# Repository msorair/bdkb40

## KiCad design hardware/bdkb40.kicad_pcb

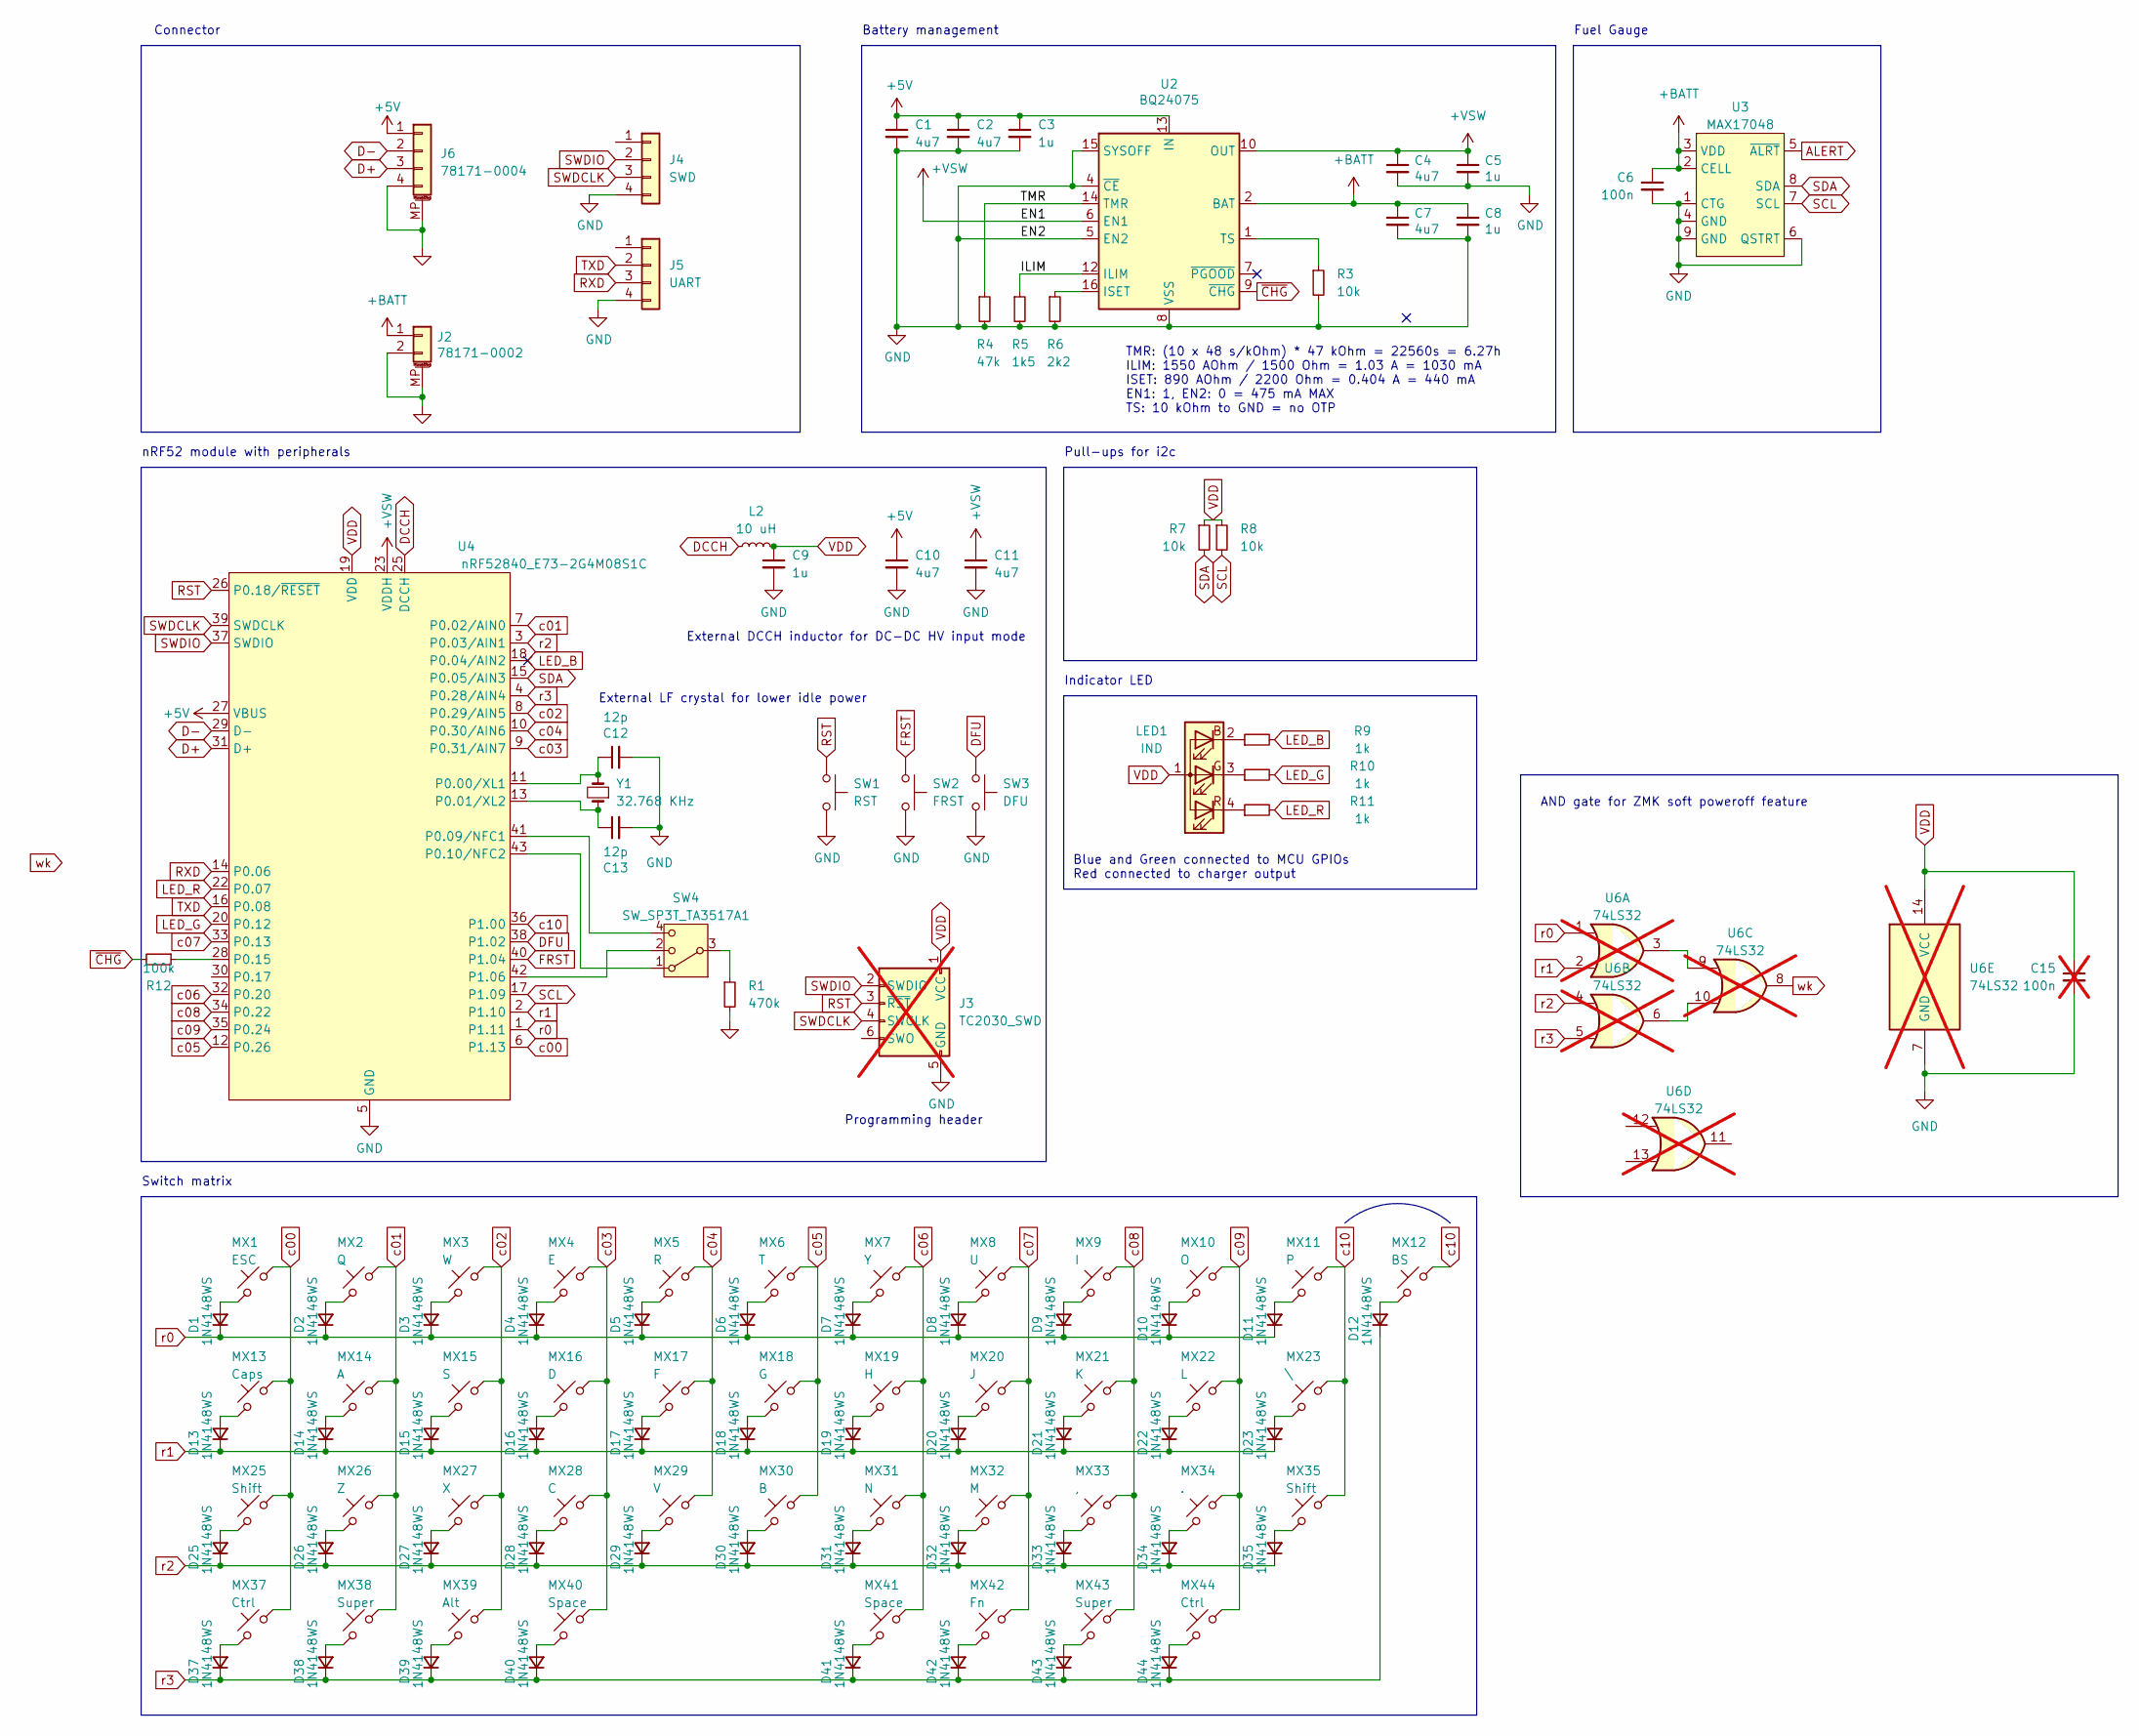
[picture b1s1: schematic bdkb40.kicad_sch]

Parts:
C1, C2, C4, C7, C10, C11: 4u7; C_0402_1005Metric; LCSC C23733
C3, C5, C8, C9: 1u; C_0402_1005Metric; LCSC C52923
C6: 100n; C_0402_1005Metric; LCSC C307331
C12, C13: 12p; C_0402_1005Metric; LCSC C1547
C15: 100n; C_0402_1005Metric; LCSC C307331; not fitted
D1, D2, D3, D4, D5, D6, D7, D8, D9, D10, D11, D12, D13, D14, D15, D16, D17, D18, D19, D20, D21, D22, D23, D25, D26, D27, D28, D29, D30, D31, D32, D33, D34, D35, D37, D38, D39, D40, D41, D42, D43, D44: 1N4148WS; D_SOD-323; LCSC C2128
J2: 78171-0002; Molex_Pico-EZmate_78171-0002_1x02-1MP_P1.20mm_Vertical; LCSC C505023
J3: TC2030_SWD; CON_TC2030_outlined; not fitted
J4: SWD; PinHeader_1x04_P2.54mm_Vertical
J5: UART; PinHeader_1x04_P2.54mm_Vertical
J6: 78171-0004; Molex_Pico-EZmate_78171-0004_1x04-1MP_P1.20mm_Vertical; LCSC C588524
L2: 10 uH; L_0603_1608Metric; LCSC C92982
LED1: IND; LED_1206R; LCSC C2802677
MX1: ESC; SW_MX_HS_CPG151101S11_1u; LCSC C5184526
MX2: Q; SW_MX_HS_CPG151101S11_1u; LCSC C5184526
MX3: W; SW_MX_HS_CPG151101S11_1u; LCSC C5184526
MX4: E; SW_MX_HS_CPG151101S11_1u; LCSC C5184526
MX5: R; SW_MX_HS_CPG151101S11_1u; LCSC C5184526
MX6: T; SW_MX_HS_CPG151101S11_1u; LCSC C5184526
MX7: Y; SW_MX_HS_CPG151101S11_1u; LCSC C5184526
MX8: U; SW_MX_HS_CPG151101S11_1u; LCSC C5184526
MX9: I; SW_MX_HS_CPG151101S11_1u; LCSC C5184526
MX10: O; SW_MX_HS_CPG151101S11_1u; LCSC C5184526
MX11: P; SW_MX_HS_CPG151101S11_1u; LCSC C5184526
MX12: BS; SW_MX_HS_CPG151101S11_1u; LCSC C5184526
MX13: Caps; SW_MX_HS_CPG151101S11_1.25u; LCSC C5184526
MX14: A; SW_MX_HS_CPG151101S11_1u; LCSC C5184526
MX15: S; SW_MX_HS_CPG151101S11_1u; LCSC C5184526
MX16: D; SW_MX_HS_CPG151101S11_1u; LCSC C5184526
MX17: F; SW_MX_HS_CPG151101S11_1u; LCSC C5184526
MX18: G; SW_MX_HS_CPG151101S11_1u; LCSC C5184526
MX19: H; SW_MX_HS_CPG151101S11_1u; LCSC C5184526
MX20: J; SW_MX_HS_CPG151101S11_1u; LCSC C5184526
MX21: K; SW_MX_HS_CPG151101S11_1u; LCSC C5184526
MX22: L; SW_MX_HS_CPG151101S11_1u; LCSC C5184526
MX23: \; SW_MX_HS_CPG151101S11_1.75u; LCSC C5184526
MX25: Shift; SW_MX_HS_CPG151101S11_1.75u; LCSC C5184526
MX26: Z; SW_MX_HS_CPG151101S11_1u; LCSC C5184526
MX27: X; SW_MX_HS_CPG151101S11_1u; LCSC C5184526
MX28: C; SW_MX_HS_CPG151101S11_1u; LCSC C5184526
MX29: V; SW_MX_HS_CPG151101S11_1u; LCSC C5184526
MX30: B; SW_MX_HS_CPG151101S11_1u; LCSC C5184526
MX31: N; SW_MX_HS_CPG151101S11_1u; LCSC C5184526
MX32: M; SW_MX_HS_CPG151101S11_1u; LCSC C5184526
MX33: ,; SW_MX_HS_CPG151101S11_1u; LCSC C5184526
MX34: .; SW_MX_HS_CPG151101S11_1u; LCSC C5184526
MX35: Shift; SW_MX_HS_CPG151101S11_1.25u; LCSC C5184526
MX37, MX44: Ctrl; SW_MX_HS_CPG151101S11_1.25u; LCSC C5184526
MX38, MX43: Super; SW_MX_HS_CPG151101S11_1u; LCSC C5184526
MX39: Alt; SW_MX_HS_CPG151101S11_1.25u; LCSC C5184526
MX40: Space; SW_MX_HS_CPG151101S11_2.25u; LCSC C5184526
MX41: Space; SW_MX_HS_CPG151101S11_2.75u; LCSC C5184526
MX42: Fn; SW_MX_HS_CPG151101S11_1.25u; LCSC C5184526
R1: 470k; R_0402_1005Metric; LCSC C23164
R3: 10k; R_0402_1005Metric; LCSC C25197
R4: 47k; R_0402_1005Metric; LCSC C25792
R5: 1k5; R_0402_1005Metric; LCSC C25867
R6: 2k2; R_0402_1005Metric; LCSC C25879
R7, R8: 10k; R_0402_1005Metric; LCSC C25744
R9, R10, R11: 1k; R_0402_1005Metric; LCSC C11702
R12: 100k; R_0402_1005Metric; LCSC C25744
SW1: RST; SW_SPST_TS-1088-xR025; LCSC C720477
SW2: FRST; SW_SPST_TS-1088-xR025; LCSC C720477
SW3: DFU; SW_SPST_TS-1088-xR025; LCSC C720477
SW4: SW_SP3T_TA3517A1; SW_SP3T_PCM13; LCSC C514001
U2: BQ24075; VQFN-16-1EP_3x3mm_P0.5mm_EP1.6x1.6mm; LCSC C15464
U3: MAX17048; DFN-8-1EP_2x2mm_P0.5mm_EP0.7x1.3mm; LCSC C2682616
U4: nRF52840_E73-2G4M08S1C; LCSC C356849
U6: 74LS32; DIP-14_W7.62mm_SMDSocket_SmallPads; not fitted
Y1: 32.768 KHz; Crystal_SMD_2012-2Pin_2.0x1.2mm; LCSC C20148

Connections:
+5V: C1.1, C2.1, C3.1, C10.1, J6.1, U2.13 (IN), U4.27 (VBUS)
+BATT: C6.1, C7.1, C8.1, J2.1, U2.2 (BAT), U2.3 (BAT), U3.2 (CELL), U3.3 (VDD)
+VSW: C4.1, C5.1, C11.1, U2.6 (EN1), U2.10 (OUT), U2.11 (OUT), U4.23 (VDDH)
/ILIM: R5.1, U2.12 (ILIM)
/TMR: R4.1, U2.14 (TMR)
ALERT: U3.5 (~ALRT)
D+: J6.3, U4.31 (D+)
D-: J6.2, U4.29 (D-)
DCCH: L2.1, U4.25 (DCCH)
DFU: SW3.1, U4.38 (P1.02)
FRST: SW2.1, U4.40 (P1.04)
GND: C1.2, C2.2, C3.2, C4.2, C5.2, C6.2, C7.2, C8.2, C9.2, C10.2, C11.2, C12.2, C13.2, C15.2, J2.2, J2.MP (MountPin), J3.5 (GND), J4.4, J5.4, J6.4, J6.MP (MountPin), R1.2, R3.2, R4.2, R5.2, R6.2, SW1.2, SW2.2, SW3.2, U2.4 (~CE), U2.5 (EN2), U2.8 (VSS), U2.15 (SYSOFF), U2.17 (VSS), U3.1 (CTG), U3.4 (GND), U3.6 (QSTRT), U3.9 (GND), U4.5 (GND), U4.21 (GND), U4.24 (GND), U6.7 (GND)
LED_B: R9.2, U4.18 (P0.04/AIN2)
LED_G: R10.2, U4.20 (P0.12)
LED_R: R11.2, U4.22 (P0.07)
unnamed: D1.2 (A), MX1.1
unnamed: D2.2 (A), MX2.1
unnamed: D3.2 (A), MX3.1
unnamed: D4.2 (A), MX4.1
unnamed: D5.2 (A), MX5.1
unnamed: D6.2 (A), MX6.1
unnamed: D7.2 (A), MX7.1
unnamed: D8.2 (A), MX8.1
unnamed: D9.2 (A), MX9.1
unnamed: D10.2 (A), MX10.1
unnamed: D11.2 (A), MX11.1
unnamed: D12.2 (A), MX12.1
unnamed: D13.2 (A), MX13.1
unnamed: D14.2 (A), MX14.1
unnamed: D15.2 (A), MX15.1
unnamed: D16.2 (A), MX16.1
unnamed: D17.2 (A), MX17.1
unnamed: D18.2 (A), MX18.1
unnamed: D19.2 (A), MX19.1
unnamed: D20.2 (A), MX20.1
unnamed: D21.2 (A), MX21.1
unnamed: D22.2 (A), MX22.1
unnamed: D23.2 (A), MX23.1
unnamed: D25.2 (A), MX25.1
unnamed: D26.2 (A), MX26.1
unnamed: D27.2 (A), MX27.1
unnamed: D28.2 (A), MX28.1
unnamed: D29.2 (A), MX29.1
unnamed: D30.2 (A), MX30.1
unnamed: D31.2 (A), MX31.1
unnamed: D32.2 (A), MX32.1
unnamed: D33.2 (A), MX33.1
unnamed: D34.2 (A), MX34.1
unnamed: D35.2 (A), MX35.1
unnamed: D37.2 (A), MX37.1
unnamed: D38.2 (A), MX38.1
unnamed: D39.2 (A), MX39.1
unnamed: D40.2 (A), MX40.1
unnamed: D41.2 (A), MX41.1
unnamed: D42.2 (A), MX42.1
unnamed: D43.2 (A), MX43.1
unnamed: D44.2 (A), MX44.1
unnamed: LED1.2 (BK), R9.1
unnamed: LED1.3 (GK), R10.1
unnamed: LED1.4 (RK), R11.1
unnamed: R1.1, SW4.3
unnamed: R6.1, U2.16 (ISET)
unnamed: R3.1, U2.1 (TS)
unnamed: C12.1, U4.11 (P0.00/XL1), Y1.2
unnamed: C13.1, U4.13 (P0.01/XL2), Y1.1
unnamed: SW4.4, U4.41 (P0.09/NFC1)
unnamed: SW4.1, U4.43 (P0.10/NFC2)
unnamed: R12.1, U4.28 (P0.15)
unnamed: SW4.2, U4.42 (P1.06)
unnamed: U6.3, U6.9
unnamed: U6.6, U6.10
RST: J3.3 (~RST), SW1.1, U4.26 (P0.18/~RESET)
RXD: J5.3, U4.14 (P0.06)
SCL: R8.2, U3.7 (SCL), U4.17 (P1.09)
SDA: R7.2, U3.8 (SDA), U4.15 (P0.05/AIN3)
SWDCLK: J3.4 (SWCLK), J4.3, U4.39 (SWDCLK)
SWDIO: J3.2 (SWDIO), J4.2, U4.37 (SWDIO)
TXD: J5.2, U4.16 (P0.08)
VDD: C9.1, C15.1, J3.1 (VCC), L2.2, LED1.1 (A), R7.1, R8.1, U4.19 (VDD), U6.14 (VCC)
c00: MX1.2, MX13.2, MX25.2, MX37.2, U4.6 (P1.13)
c01: MX2.2, MX14.2, MX26.2, MX38.2, U4.7 (P0.02/AIN0)
c02: MX3.2, MX15.2, MX27.2, MX39.2, U4.8 (P0.29/AIN5)
c03: MX4.2, MX16.2, MX28.2, MX40.2, U4.9 (P0.31/AIN7)
c04: MX5.2, MX17.2, MX29.2, U4.10 (P0.30/AIN6)
c05: MX6.2, MX18.2, MX30.2, U4.12 (P0.26)
c06: MX7.2, MX19.2, MX31.2, MX41.2, U4.32 (P0.20)
c07: MX8.2, MX20.2, MX32.2, MX42.2, U4.33 (P0.13)
c08: MX9.2, MX21.2, MX33.2, MX43.2, U4.34 (P0.22)
c09: MX10.2, MX22.2, MX34.2, MX44.2, U4.35 (P0.24)
c10: MX11.2, MX12.2, MX23.2, MX35.2, U4.36 (P1.00)
r0: D1.1 (K), D2.1 (K), D3.1 (K), D4.1 (K), D5.1 (K), D6.1 (K), D7.1 (K), D8.1 (K), D9.1 (K), D10.1 (K), D11.1 (K), U4.1 (P1.11), U6.1
r1: D13.1 (K), D14.1 (K), D15.1 (K), D16.1 (K), D17.1 (K), D18.1 (K), D19.1 (K), D20.1 (K), D21.1 (K), D22.1 (K), D23.1 (K), U4.2 (P1.10), U6.2
r2: D25.1 (K), D26.1 (K), D27.1 (K), D28.1 (K), D29.1 (K), D30.1 (K), D31.1 (K), D32.1 (K), D33.1 (K), D34.1 (K), D35.1 (K), U4.3 (P0.03/AIN1), U6.4
r3: D12.1 (K), D37.1 (K), D38.1 (K), D39.1 (K), D40.1 (K), D41.1 (K), D42.1 (K), D43.1 (K), D44.1 (K), U4.4 (P0.28/AIN4), U6.5
~CHG: R12.2, U2.9 (~CHG)

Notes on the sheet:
AND gate for ZMK soft poweroff feature
Indicator LED
Pull-ups for i2c
External DCCH inductor for DC-DC HV input mode
Programming header
Blue and Green connected to MCU GPIOs Red connected to charger output
Connector
TMR: (10 x 48 s/kOhm) * 47 kOhm = 22560s = 6.27h ILIM: 1550 AOhm / 1500 Ohm = 1.03 A = 1030 mA ISET: 890 AOhm / 2200 Ohm = 0.404 A = 440 mA EN1: 1, EN2: 0 = 475 mA MAX TS: 10 kOhm to GND = no OTP
Switch matrix
Fuel Gauge
Battery management
nRF52 module with peripherals
External LF crystal for lower idle power

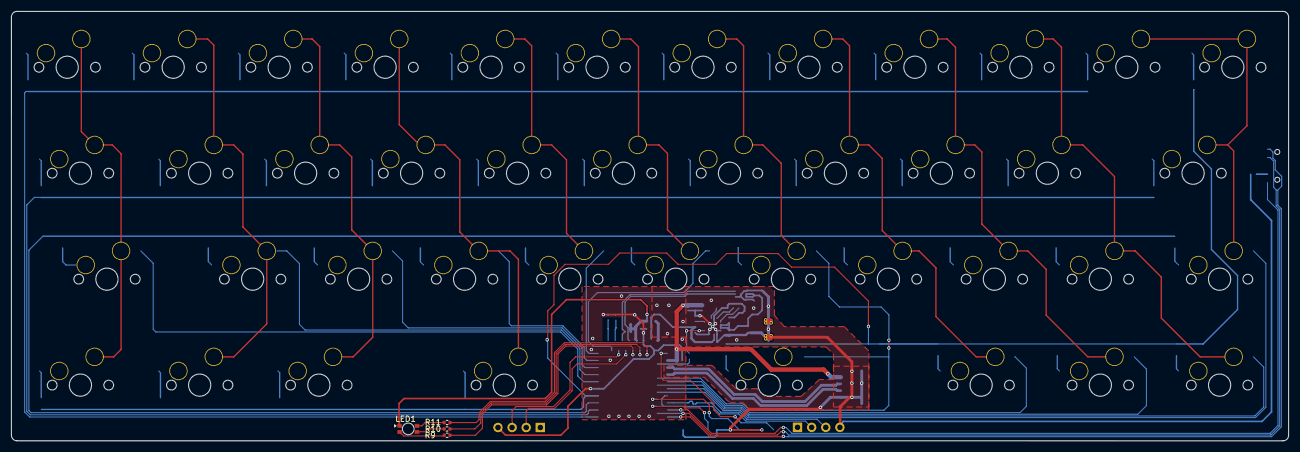
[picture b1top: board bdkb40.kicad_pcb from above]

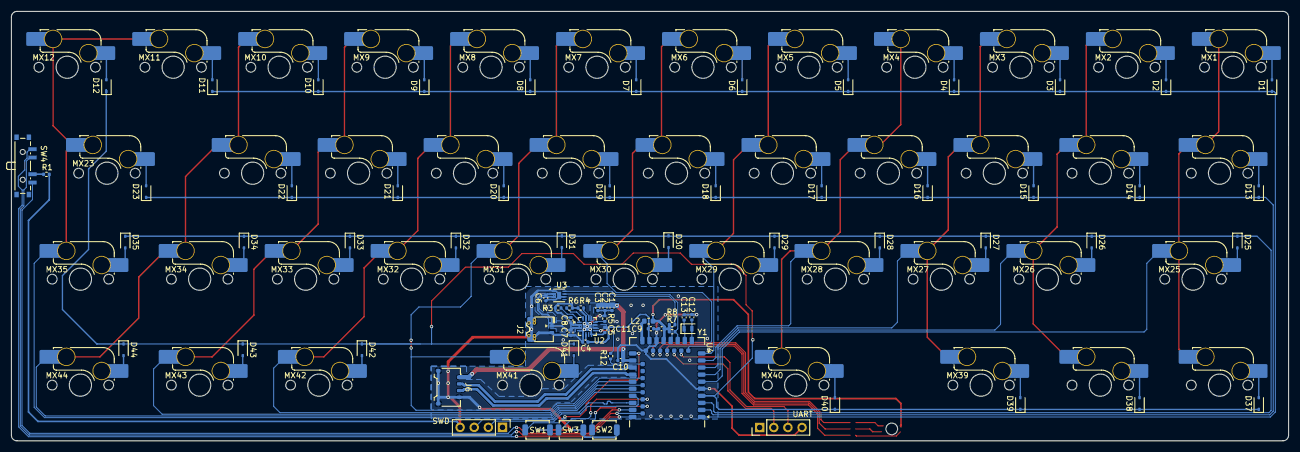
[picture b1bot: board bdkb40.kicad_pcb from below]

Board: 2 copper layers, 229.6 x 77.2 mm, 122 parts (118 on the bottom side), 92 nets.

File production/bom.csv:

Designator,Footprint,Quantity,Value,LCSC Part #
"C1, C10, C11, C2, C4, C7",0402,6,4u7,C23733
"C12, C13",0402,2,12p,C1547
"C3, C5, C8, C9",0402,4,1u,C52923
C6,0402,1,100n,C307331
"D1, D10, D11, D12, D13, D14, D15, D16, D17, D18, D19, D2, D20, D21, D22, D23, D25, D26, D27, D28, D29, D3, D30, D31, D32, D33, D34, D35, D37, D38, D39, D4, D40, D41, D42, D43, D44, D5, D6, D7, D8, D9",D_SOD-323,42,1N4148WS,C2128
J2,Molex_Pico-EZmate_78171-0002_1x02-1MP_P1.20mm_Vertical,1,78171-0002,C505023
J4,PinHeader_1x04_P2.54mm_Vertical,1,SWD,
J5,PinHeader_1x04_P2.54mm_Vertical,1,UART,
J6,Molex_Pico-EZmate_78171-0004_1x04-1MP_P1.20mm_Vertical,1,78171-0004,C588524
L2,0603,1,10 uH,C92982
LED1,LED_1206R,1,IND,C2802677
MX1,SW_MX_HS_CPG151101S11_1u,1,ESC,C5184526
MX10,SW_MX_HS_CPG151101S11_1u,1,O,C5184526
MX11,SW_MX_HS_CPG151101S11_1u,1,P,C5184526
MX12,SW_MX_HS_CPG151101S11_1u,1,BS,C5184526
MX13,SW_MX_HS_CPG151101S11_1.25u,1,Caps,C5184526
MX14,SW_MX_HS_CPG151101S11_1u,1,A,C5184526
MX15,SW_MX_HS_CPG151101S11_1u,1,S,C5184526
MX16,SW_MX_HS_CPG151101S11_1u,1,D,C5184526
MX17,SW_MX_HS_CPG151101S11_1u,1,F,C5184526
MX18,SW_MX_HS_CPG151101S11_1u,1,G,C5184526
MX19,SW_MX_HS_CPG151101S11_1u,1,H,C5184526
MX2,SW_MX_HS_CPG151101S11_1u,1,Q,C5184526
MX20,SW_MX_HS_CPG151101S11_1u,1,J,C5184526
MX21,SW_MX_HS_CPG151101S11_1u,1,K,C5184526
MX22,SW_MX_HS_CPG151101S11_1u,1,L,C5184526
MX23,SW_MX_HS_CPG151101S11_1.75u,1,\,C5184526
MX25,SW_MX_HS_CPG151101S11_1.75u,1,Shift,C5184526
MX26,SW_MX_HS_CPG151101S11_1u,1,Z,C5184526
MX27,SW_MX_HS_CPG151101S11_1u,1,X,C5184526
MX28,SW_MX_HS_CPG151101S11_1u,1,C,C5184526
MX29,SW_MX_HS_CPG151101S11_1u,1,V,C5184526
MX3,SW_MX_HS_CPG151101S11_1u,1,W,C5184526
MX30,SW_MX_HS_CPG151101S11_1u,1,B,C5184526
MX31,SW_MX_HS_CPG151101S11_1u,1,N,C5184526
MX32,SW_MX_HS_CPG151101S11_1u,1,M,C5184526
MX33,SW_MX_HS_CPG151101S11_1u,1,",",C5184526
MX34,SW_MX_HS_CPG151101S11_1u,1,.,C5184526
MX35,SW_MX_HS_CPG151101S11_1.25u,1,Shift,C5184526
"MX37, MX44",SW_MX_HS_CPG151101S11_1.25u,2,Ctrl,C5184526
"MX38, MX43",SW_MX_HS_CPG151101S11_1u,2,Super,C5184526
MX39,SW_MX_HS_CPG151101S11_1.25u,1,Alt,C5184526
MX4,SW_MX_HS_CPG151101S11_1u,1,E,C5184526
MX40,SW_MX_HS_CPG151101S11_2.25u,1,Space,C5184526
MX41,SW_MX_HS_CPG151101S11_2.75u,1,Space,C5184526
MX42,SW_MX_HS_CPG151101S11_1.25u,1,Fn,C5184526
MX5,SW_MX_HS_CPG151101S11_1u,1,R,C5184526
MX6,SW_MX_HS_CPG151101S11_1u,1,T,C5184526
MX7,SW_MX_HS_CPG151101S11_1u,1,Y,C5184526
MX8,SW_MX_HS_CPG151101S11_1u,1,U,C5184526
MX9,SW_MX_HS_CPG151101S11_1u,1,I,C5184526
R1,0402,1,470k,C23164
"R10, R11, R9",0402,3,1k,C11702
R12,0402,1,100k,C25744
R3,0402,1,10k,C25197
R4,0402,1,47k,C25792
R5,0402,1,1k5,C25867
R6,0402,1,2k2,C25879
"R7, R8",0402,2,10k,C25744
SW1,SW_T1A2QR,1,RST,C100056
SW2,SW_T1A2QR,1,FRST,C100056
SW3,SW_T1A2QR,1,DFU,C100056
SW4,SW_SP3T_PCM13,1,SW_SP3T,
U2,VQFN-16-1EP_3x3mm_P0.5mm_EP1.6x1.6mm,1,BQ24075,C15464
U3,DFN-8-1EP_2x2mm_P0.5mm_EP0.7x1.3mm,1,MAX17048,C2682616
U4,nRF52840_E73-2G4M08S1C,1,nRF52840_E73-2G4M08S1C,C356849
Y1,Crystal_SMD_2012-2Pin_2.0x1.2mm,1,32.768 KHz,C20148

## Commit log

2025-12-21 pcb design move to hardware folder
2025-12-21 Add support for generating plate and statilizer
2025-12-21 Add support for generating gasket plate
2026-01-04 support top mount case
2026-01-05 add fillet for top mount
2026-01-07 add heatset hole for top mount case
2026-01-07 update pcb
2026-01-09 add bottom plate
2026-01-17 add rib for plate
2026-01-17 update top_mount
2026-01-17 update plate
2026-01-17 update pcd
2026-03-20 update fabrication info
